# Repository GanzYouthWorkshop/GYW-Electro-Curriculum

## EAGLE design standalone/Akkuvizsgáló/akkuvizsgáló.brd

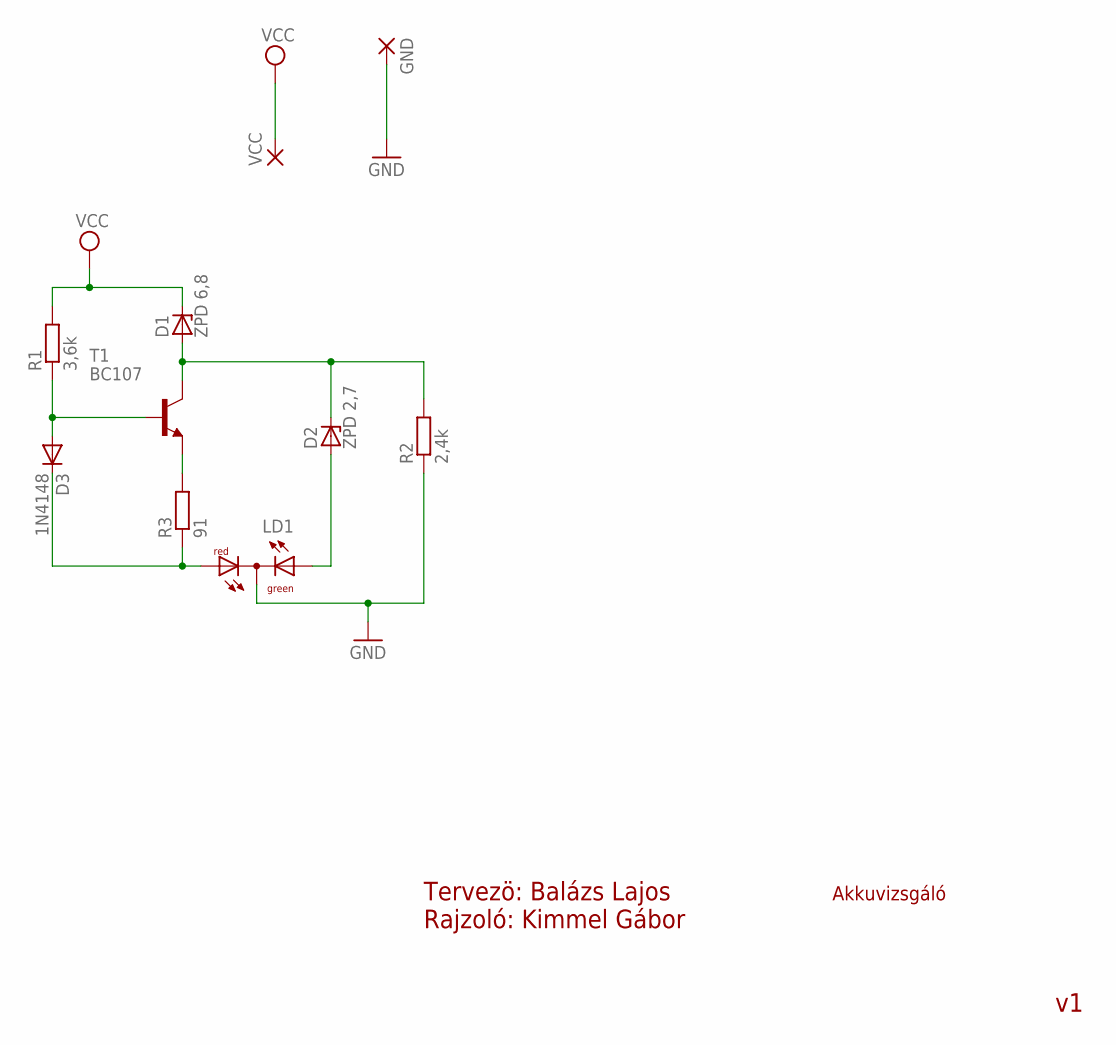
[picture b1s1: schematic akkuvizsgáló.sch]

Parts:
D1: ZPD 6,8; DO35Z10
D2: ZPD 2,7; DO35Z10
D3: 1N4148; DO35-10
GND: 2,15/1,0
LD1: DUOLED-RG-C; DUOLED-C-5MM
R1: 3,6k; 0204/7
R2: 2,4k; 0204/7
R3: 91; 0204/7
T1: BC107; TO18
VCC: 2,15/1,0

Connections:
GND: GND.1, LD1.C, R2.1
unnamed: R3.2, T1.1 (E)
unnamed: D3.A, R1.1, T1.2 (B)
unnamed: D3.C, LD1.AR, R3.1
unnamed: D1.A, D2.C, R2.2, T1.3 (C)
unnamed: D2.A, LD1.AX (AG)
VCC: D1.C, R1.2, VCC.1

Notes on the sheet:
Akkuvizsgáló
Tervezö: Balázs Lajos Rajzoló: Kimmel Gábor

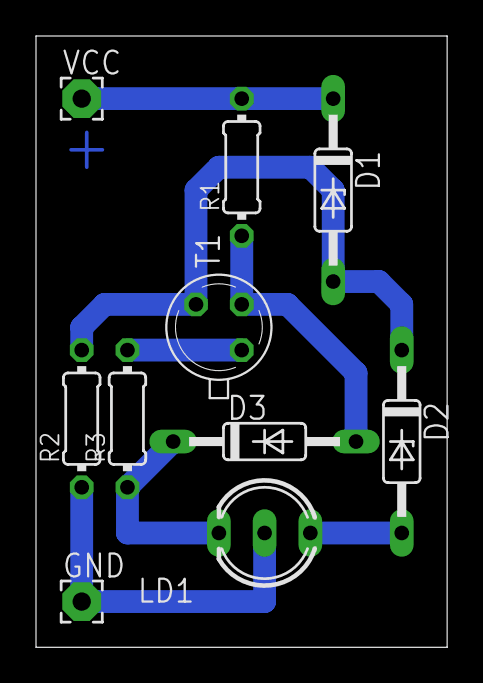
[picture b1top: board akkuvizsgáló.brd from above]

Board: 2 copper layers, 22.8 x 34.0 mm, 10 parts (0 on the bottom side), 7 nets.

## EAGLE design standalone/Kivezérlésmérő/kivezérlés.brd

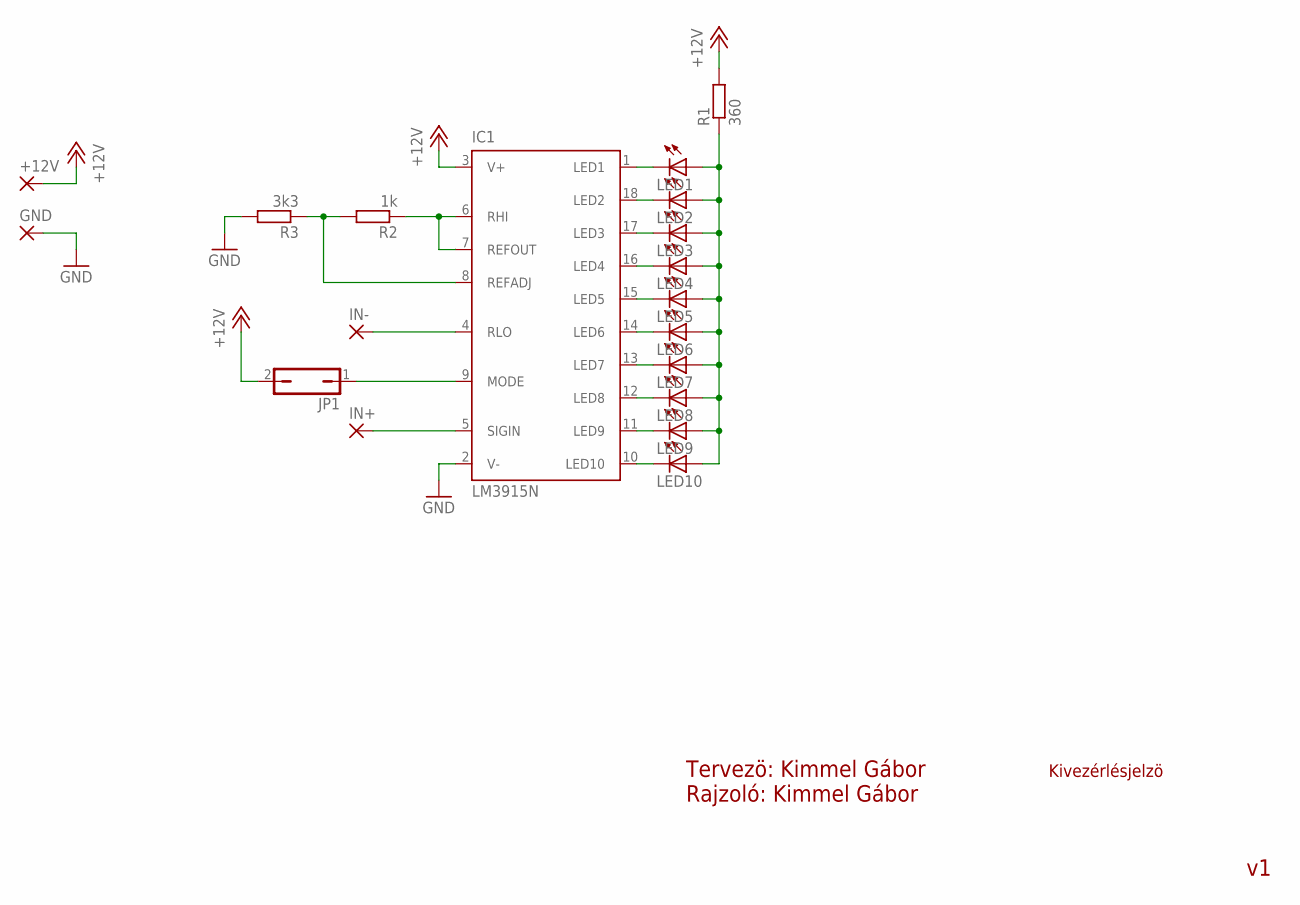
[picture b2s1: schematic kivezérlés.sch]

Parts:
+12V: 2,15/1,0
GND: 2,15/1,0
IC1: LM3915N; DIL18
IN+: 2,15/1,0
IN-: 2,15/1,0
JP1: JP1Q; JP1
LED1, LED2, LED3, LED4, LED5, LED6, LED7, LED8, LED9, LED10: LED5MM
R1: 360; 0309/12
R2: 1k; 0309/12
R3: 3k3; 0309/12

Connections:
+12V: +12V.1, IC1.3 (V+), JP1.2, R1.2
GND: GND.1, IC1.2 (V-), R3.2
unnamed: IC1.9 (MODE), JP1.1
unnamed: IC1.6 (RHI), IC1.7 (REFOUT), R2.1
unnamed: IC1.8 (REFADJ), R2.2, R3.1
unnamed: IC1.4 (RLO), IN-.1
unnamed: IC1.5 (SIGIN), IN+.1
unnamed: IC1.1 (LED1), LED1.K (C)
unnamed: IC1.18 (LED2), LED2.K (C)
unnamed: IC1.17 (LED3), LED3.K (C)
unnamed: IC1.16 (LED4), LED4.K (C)
unnamed: IC1.15 (LED5), LED5.K (C)
unnamed: IC1.14 (LED6), LED6.K (C)
unnamed: IC1.13 (LED7), LED7.K (C)
unnamed: IC1.12 (LED8), LED8.K (C)
unnamed: IC1.11 (LED9), LED9.K (C)
unnamed: IC1.10 (LED10), LED10.K (C)
unnamed: LED1.A, LED2.A, LED3.A, LED4.A, LED5.A, LED6.A, LED7.A, LED8.A, LED9.A, LED10.A, R1.1

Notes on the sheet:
Kivezérlésjelzö
Tervezö: Kimmel Gábor Rajzoló: Kimmel Gábor

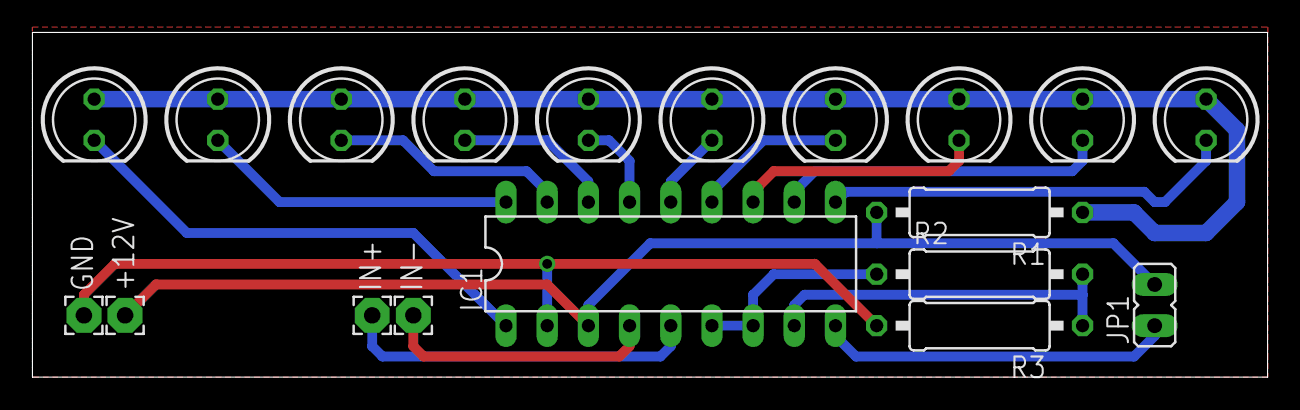
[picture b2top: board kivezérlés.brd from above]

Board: 2 copper layers, 76.2 x 21.3 mm, 19 parts (0 on the bottom side), 18 nets.

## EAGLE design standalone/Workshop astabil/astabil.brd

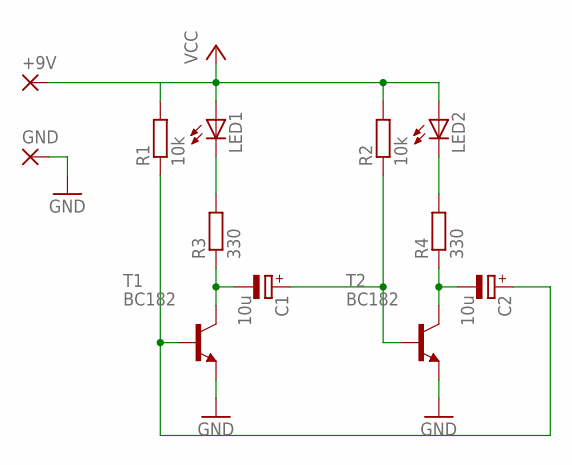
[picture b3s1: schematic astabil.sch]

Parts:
+9V: 2,54/1,0
C1, C2: 10u; E3,5-8
GND: 2,54/1,0
LED1, LED2: LED5MM
R1, R2: 10k; 0207/10
R3, R4: 330; 0207/10
T1, T2: BC182; TO92-CBE

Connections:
GND: GND.1, T1.E, T2.E
unnamed: C2.+, R1.1, T1.B
unnamed: C1.+, R2.1, T2.B
unnamed: C1.-, R3.1, T1.C
unnamed: LED1.K (C), R3.2
unnamed: C2.-, R4.1, T2.C
unnamed: LED2.K (C), R4.2
VCC: +9V.1, LED1.A, LED2.A, R1.2, R2.2

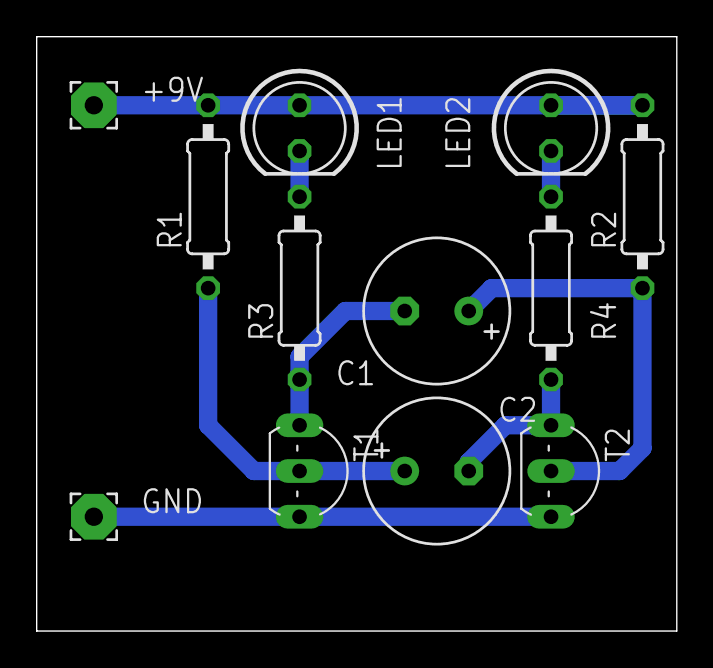
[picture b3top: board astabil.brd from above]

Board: 2 copper layers, 35.6 x 33.0 mm, 12 parts (0 on the bottom side), 8 nets.
